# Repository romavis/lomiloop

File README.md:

# About

**Lomiloop** is a wideband directional receiving loop antenna amplifier.

With it, you can build antennas that look like [this](docs/ant1.jpg).

It was designed for thick single-turn coreless loops with high area and low
inductance, that are electrically small compared to the wavelength of received
signal. With ~1.0m dia. loop, this allows to build an antenna that is
moderately portable, wideband, displaying almost flat antenna factor throughout
band of interest (approx. 50 kHz to 10 MHz), and has high enough sensitivity and
discrimination of near-field E-field noise sources that it can be used for
receiving LF and MF bands in urban areas. Usage of HF is possible, although not
recommended due to:
- Antenna noise which is noticeably higher than the atmospheric noise in HF band
- Wave effects in the loop on frequencies above ~15 MHz.

# Schematic and PCB

All the files here were designed in KiCad 5.1.10.

Schematic is also available in [PDF format](docs/schematic.pdf).

The PCB that is presented in this repository was specifically designed for
*Gainta G113* aluminium housing (also sold under Velleman brand in EU). For coax
connection, it uses female SMA connector to which BNC-SMA pigtail is then
connected, and Keystone 7771 screw terminals for loop connection. Actual loop is
wired to the binding posts which are mounted on the housing and then wired to
the Keystone terminals on the PCB.

Photos of assembled PCB:

<table>
  <tr>
    <td></td>
    <td></td>
   </tr> 
</table>

# Loop selection

Author uses D=90cm circular loop made from aluminium pipe d=15mm with wall
thickness s=1mm. This loop has a measured inductance of 2.46 uH at 1 MHz.

Originally it was an anodized aluminium hulahoop from NiroSport brand, ends of
which have been spread, a middle d=16mm aluminium pipe have been added and fixed
in place using T-pieces and epoxy. The end result is visible on the 
photo:

# Background

Long ago I became interested in reception of long- & mid-wave radio stations -
it all started with an unfinished
[Loran C receiver](https://github.com/RomaVis/LoranC) project that I've designed
for my BSc.

What that project made clear is that reception of LW/MW/HF signals in the
typical urban setting is challenging and in many cases impossible due to
man-made noise sources such as unfiltered cheapo switching power supplies,
HomePlug / PLT adapters, etc.

Of course, some noise filtering can be done later down the chain (e.g. in DSP in
case of an SDR receiver), but it's well known that any radio begins with an
antenna: the antenna amplifier usually sets the noise floor of the system and
antenna is usually the only element that has access to physical quantities that
are not representable after the signal gets into the cable, such as EM wave
direction and E-to-H field ratio. Being able to improve SNR by using a proper
antenna design will make further signal processing significantly simpler and
sometimes is a factor that determines whether the signal can be received or not,
no matter how complicated the DSP processing is.

Antenna design that is well-suited to urban usage on LW/MW bands is a
[loop antenna](https://en.wikipedia.org/wiki/Loop_antenna) which has two key
traits:
- Directivity pattern with strong null in two directions.
- Predominantly H-field sensitivity.

This allows to "null out" a single point-like noise source, as well as, compared
to "E-field" antennas such as MiniWhip, reduce receiver sensitivity to the
man-made noise that comes from unefficient near-field radiators that produce EM
field wherein [wave impedance](https://en.wikipedia.org/wiki/Wave_impedance) is
significantly higher than the
[impedance of free space](https://en.wikipedia.org/wiki/Impedance_of_free_space).

# Circuit description

See schematic in [PDF](docs/schematic.pdf).

Signal path in the amplifier is as follows:
- J1, J2 - screw terminals to which loop is connected.
- T1 - DC-isolation transformer for the loop.
- Q1, Q2, T2 - differential common base amplifier with augmentation.
- Q3, Q4 - emitter follower.
- Q5, Q6 - differential amplifier with 200 ohm output impedance.
- T3 - output 200/50 ohm balun to drive coax line.
- J4 - 50-ohm coaxial cable connector that carries output signal (AC) as well as
  supply voltage for the amplifier (DC).

One of design goals for the amplifier was to present very *low* impedance to the
loop, around 0.5-1.0 Ohm. Loop loaded with active impedance exhibits a high-pass
response, where cutoff frequency *decreases* as amplifier impedance *decreases*.
To achieve a cutoff on the order of 50-100kHz with common loop inductances (2-4
uH) input impedance of the amplifier should be this low.

Transformer T1 provides DC isolation of the loop, which is necessary since right
side of it (looking at the schematic) is biased to approx. ~1.7V w.r.t. ground.
R1, R2 are static leakage resistors that prevent static charge builtup if a
fully isolated loop is connected to the amplifier input terminals.

Differential common-base stage Q1, Q2 functions as a transimpedance amplifier,
converting input current coming from the loop into voltage on R8-R9. C10, C11,
C12, C13, R10 allow for correction of amplifier's response around 20-30 MHz.
This stage ultimately determines the noise floor of the whole amplifier.
Transformer T2 is an augmentation transformer that assures low input impedance.

Q3, Q4 stage increases load impedance seen by Q1, Q2 stage and allows for more
wideband response. Q5, Q6 is the output amplifier that drives output 200 ohm
balun and ultimately the 50-ohm coax cable. Total voltage gain of Q3-Q6 stages
is about +16dB, but it may be increased by changing value of R13. Resistor
network R16-19 sets the bias current of Q5-Q6 - it should also be increased if
higher gain is desired.

D2, D3, D4, D5, D6, D7, D8 normally stay in non-conducting state. These diodes
serve to prevent breakdown of amplifier's transistors when subjected to strong
input signals, and the design of protection circuit is based on LTSpice
simulations. It remains to be seen how well will this circuit perform in e.g.
summer weather with thunderstorms. Most probably some of these diodes may be
excluded.

C19, L1, C20, C21 form AC/DC splitter that separates DC supply voltage present
on the coax cable from AC RF signal. U1 together with surrounding components
provides stable 10V reference that biases all transistor stages. D1 protects
amplifier from reverse polarity DC on the coax cable or too high DC voltages -
the TVS diode starts conducting at about 18-19V, while the required antenna
supply voltage coming from the coax cable is 12 to 16 volt.

Operational amplifier U2A is connected as an integrator with differential input.
It's the central element of a DC servo feedback loop that balances currents in
all differential transistor stages. While Q2's base bias voltage is fixed, U2A
varies DC voltage on the base terminal of Q1. The balance of Q1-Q2, which is a
differential pair with no external emitter degeneration, is very sensitive to DC
bias and requires use of feedback loop to stabilize it. When Q1-Q2 are properly
biased, their DC collector currents are equal, which in turn means that
collector currents of Q5 and Q6 are equal (up to the asymmetricity of Q5 and Q6
which plays a minor role here). R22,R23 sense collector currents of Q5 and Q6,
while R14,R15,R20,R21 divide the voltage measured on R22,R23 to keep it within
the range acceptable for op.amp inputs. Operational amplifier then adjusts Q1
bias to equalize voltages on R22,R23 and thus collector currents of all
transistors.

MKT/MKP film capacitors are used for C14 and C15 - due to their rather high
capacity of 1uF and the fact that their low leakage is crucial to correct
integrator operation.

# License

Copyright 2021 Roman Dobrodii

SPDX-License-Identifier: Apache-2.0 WITH SHL-2.1

Licensed under the Solderpad Hardware License v 2.1 (the “License”); you may not
use this work except in compliance with the License, or, at your option, the
Apache License version 2.0. You may obtain a copy of the License at

https://solderpad.org/licenses/SHL-2.1/

Unless required by applicable law or agreed to in writing, any work distributed
under the License is distributed on an “AS IS” BASIS, WITHOUT WARRANTIES OR
CONDITIONS OF ANY KIND, either express or implied. See the License for the
specific language governing permissions and limitations under the License.

# References

1. [Chris Trask - A High Dynamic Range Amplifier for Wideband Active Loop Antennas](https://web.archive.org/web/20181024183035/www.home.earthlink.net/~christrask/Wideband%20Loop%20Antenna%20Amplifier.pdf)
2. [US pat 6271721B1 - Chris Trask - Common-base transistor amplifiers with linearity augmentation](https://patents.google.com/patent/US6271721B1/en)
3. [Chavdar Levkov - Wideband Active Small Magnetic Loop Antenna](https://www.lz1aq.signacor.com/docs/wsml/wideband-active-sm-loop-antenna.htm) 
4. [George Smart - WellGood loop](https://www.george-smart.co.uk/projects/wellgood_loop/)

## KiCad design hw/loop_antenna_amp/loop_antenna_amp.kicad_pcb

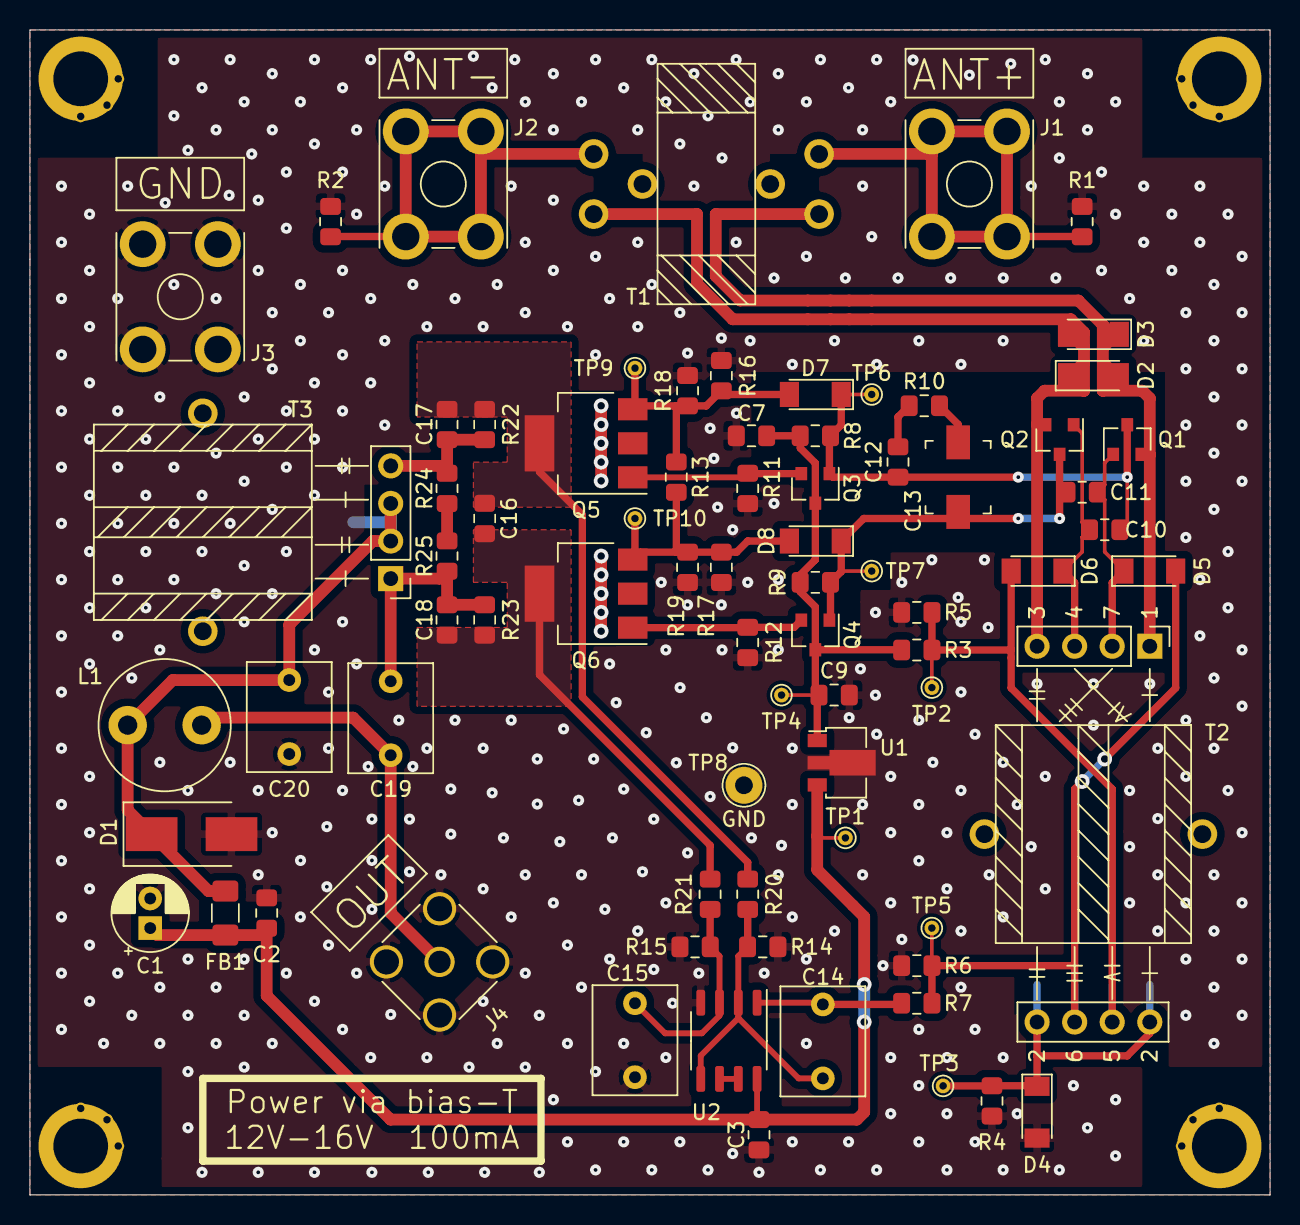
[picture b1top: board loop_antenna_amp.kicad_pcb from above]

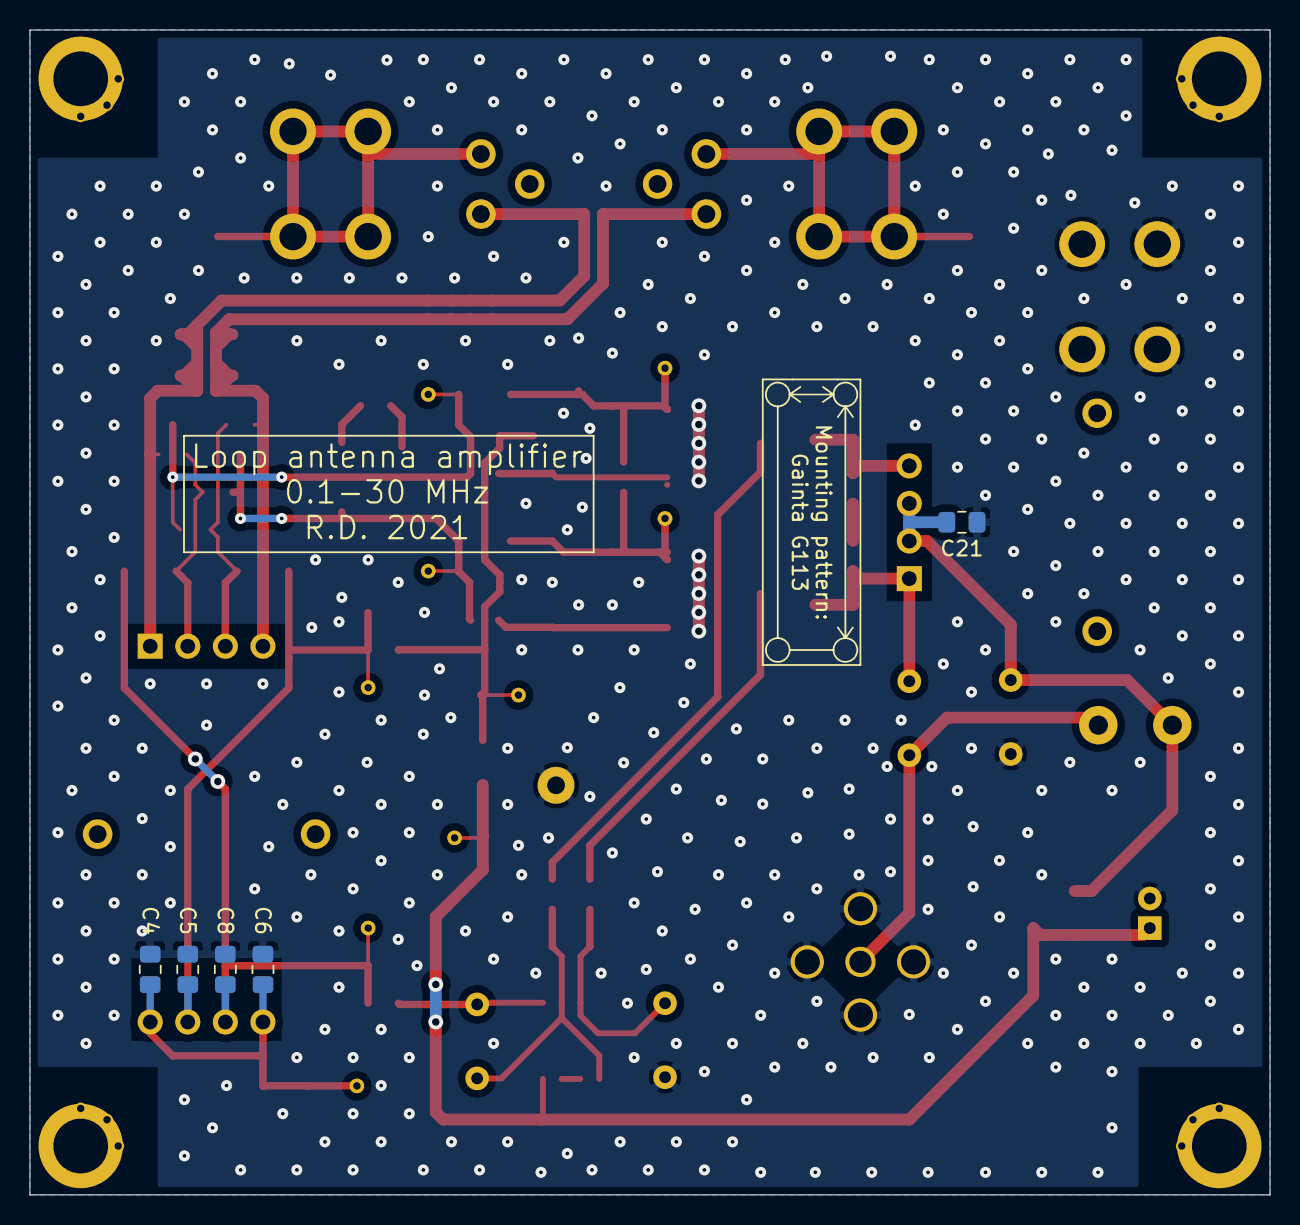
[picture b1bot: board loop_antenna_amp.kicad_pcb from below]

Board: 2 copper layers, 83.8 x 78.7 mm, 85 parts (5 on the bottom side), 31 nets.

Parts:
C1: 47u 25V; CP_Radial_D5.0mm_P2.00mm
C2, C3, C4, C5, C7, C8, C9, C17, C18, C21: 100n; C_0805_2012Metric_Pad1.15x1.40mm_HandSolder
C6: 1u; C_0805_2012Metric_Pad1.15x1.40mm_HandSolder
C10, C11: 3.3p; C_0805_2012Metric_Pad1.15x1.40mm_HandSolder
C12: 10p; C_0805_2012Metric_Pad1.15x1.40mm_HandSolder
C13: 3-10p; C_Trimmer_Murata_TZB4-A
C14, C15, C19, C20: 1u; C_Rect_L7.2mm_W5.5mm_P5.00mm_FKS2_FKP2_MKS2_MKP2
C16: DNP; C_0805_2012Metric_Pad1.15x1.40mm_HandSolder
D1: SMBJ16A; D_SMB_Handsoldering
D2, D3, D5, D6, D7, D8: LL4148; D_MiniMELF
D4: BZV55-C4V7; D_MiniMELF
FB1: Ferrite_Bead; L_1206_3216Metric_Pad1.42x1.75mm_HandSolder
H1, H2, H3, H4: MountingHole
J1: ANT+; Keystone_7771_ScrewTerminal
J2: ANT-; Keystone_7771_ScrewTerminal
J3: GND; Keystone_7771_ScrewTerminal
J4: Coax (SMA); SMA_Amphenol_132134_Vertical
L1: 1mH; L_Radial_D8.7mm_P5.00mm_Fastron_07HCP
Q1, Q2, Q3, Q4: MMBT3904; SOT-23
Q5, Q6: PZT3904; SOT-223-3_TabPin2
R1, R2: 100k; R_0805_2012Metric_Pad1.15x1.40mm_HandSolder
R3: 3.3k; R_0805_2012Metric_Pad1.15x1.40mm_HandSolder
R4, R24, R25: 100; R_0805_2012Metric_Pad1.15x1.40mm_HandSolder
R5, R6, R7, R10, R11, R12: 1k; R_0805_2012Metric_Pad1.15x1.40mm_HandSolder
R8, R9, R18, R19: 470; R_0805_2012Metric_Pad1.15x1.40mm_HandSolder
R13, R22, R23: 10; R_0805_2012Metric_Pad1.15x1.40mm_HandSolder
R14, R15, R20, R21: 10k; R_0805_2012Metric_Pad1.15x1.40mm_HandSolder
R16, R17: DNP; R_0805_2012Metric_Pad1.15x1.40mm_HandSolder
T1: Isolation trafo; FairRite_5943004901_Standing
T2: Normalization trafo; BN_43_202_Trafo1SP2S
T3: Output balun; BN_43_202_Trafo1P1S
TP1, TP2, TP3, TP4, TP5, TP6, TP7, TP9, TP10: TestPoint; TestPoint_THTPad_D1.0mm_Drill0.5mm
TP8: TestPoint; TestPoint_THTPad_D2.5mm_Drill1.2mm
U1: L78L10; SOT-89-3
U2: TL072; SO-8_3.9x4.9mm_P1.27mm

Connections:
+10V: C7.1, C9.1, Q3.3, Q4.3, R3.2, R8.2, R9.1, TP4.1, U1.1
/VFEED: C20.1, C21.1, D1.1, FB1.2, L1.1, T3.2, T3.4
GND: C1.2, C2.2, C3.2, C4.2, C5.2, C6.2, C7.2, C8.2, C9.2, C15.2, C20.2, C21.2, D1.2, D4.2, J3.1, J4.2, R1.2, R2.1, R4.2, R5.2, R6.2, R11.2, R12.1, R14.2, R15.2, R16.2, R17.1, R18.2, R19.1, TP8.1, U1.2, U2.4
unnamed: C4.1, C6.1, D4.1, R4.1, T2.2, TP3.1
unnamed: C5.1, D6.2, R3.1, R5.1, T2.5, TP2.1
unnamed: C8.1, D5.2, R6.1, R7.2, T2.6, TP5.1
unnamed: C10.1, D6.1, Q2.1, T2.4
unnamed: C10.2, C12.1, D7.1, Q1.3, Q3.1, R8.1, TP6.1
unnamed: C11.1, C13.2, D8.1, Q2.3, Q4.1, R9.2, TP7.1
unnamed: C11.2, D5.1, Q1.1, T2.7
unnamed: C12.2, R10.1
unnamed: C13.1, R10.2
unnamed: C14.1, R14.1, R20.2, U2.2, U2.5
unnamed: C14.2, R7.1, U2.1
unnamed: C15.1, R15.1, R21.2, U2.3
unnamed: C16.1, C17.2, Q5.2, R20.1, R22.1
unnamed: C16.2, C18.2, Q6.2, R21.1, R23.1
unnamed: C17.1, R22.2, R24.1, T3.3
unnamed: C18.1, C19.2, R23.2, R25.2, T3.1
unnamed: C19.1, J4.1, L1.2
unnamed: D2.1, D3.2, Q2.2, T1.3, T2.3
unnamed: D2.2, D3.1, Q1.2, T1.4, T2.1
unnamed: D7.2, Q5.3, R13.1, R16.1, R18.1, TP9.1
unnamed: D8.2, Q6.3, R13.2, R17.2, R19.2, TP10.1
unnamed: J1.1, R1.1, T1.1
unnamed: J2.1, R2.2, T1.2
unnamed: Q3.2, Q5.1, R11.1
unnamed: Q4.2, Q6.1, R12.2
unnamed: R24.2, R25.1
unnamed: U2.6, U2.7
VCC: C1.1, C2.1, C3.1, FB1.1, TP1.1, U1.3, U2.8

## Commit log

2021-06-14 Loop antenna: add schematic, license, readme template
2021-06-15 Loop antenna: annotate schematic
2021-06-15 Loop antenna: add comments to schematic
2021-06-17 Loop antenna: redraw transformer, add protection diodes based on LTSpice simulation
2021-06-18 Loop antenna: add custom footprints, assign footprints
2021-06-18 Loop antenna: leave only SMA connector (coax can be soldered there)
2021-06-23 Loop antenna: PCB layout almost completed
2021-06-23 Loop antenna: initial PCB layout completed
2021-07-01 Loop antenna: make mounting holes more stable
2021-07-01 Loop antenna: fix balun footprint
2021-07-01 Loop antenna: improve silkscreen
2021-07-06 Loop antenna: modify DC servo feedback to allow 0 ohm degeneration in output stage
2021-07-06 Loop antenna amp: remove DC bias from output balun (bias current was too high)
2021-07-06 Loop antenna amp: reannotate schematic, use bigger footprint for film caps
2021-07-06 Loop antenna amp: update PCB to match schematic
2021-07-06 Loop antenna amp: fix silkscreen references
2021-07-07 Loop antenna amp: fix some vias
2021-07-07 Loop antenna amp: simplify input protection
2021-07-07 Loop antenna amp: update PCB to match schematic, make it rectangular - remove fin
2021-07-08 Loop antenna amp: minor fixes of vias and silkscreen
2021-07-09 Loop antenna amp: fix antenna connector polarity markings
2021-07-19 Loop antenna amp: fix mounting hole footprint (remove vias)
2021-11-28 Loop antenna amp: document actual transformer design
2021-12-28 Lay out files so that it fits a dedicated repo
2021-12-28 Remove unused external symbol lib
2021-12-28 Add .gitignore
2021-12-28 Rename project and design files to 'lomiloop'
2021-12-28 Add PDF schematic, update readme
2023-03-30 README: update, add photos
